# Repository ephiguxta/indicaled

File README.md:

# indicaled
Utiliza-se nove portas como input e outras nove portas para acionar um LED relativo ao input.

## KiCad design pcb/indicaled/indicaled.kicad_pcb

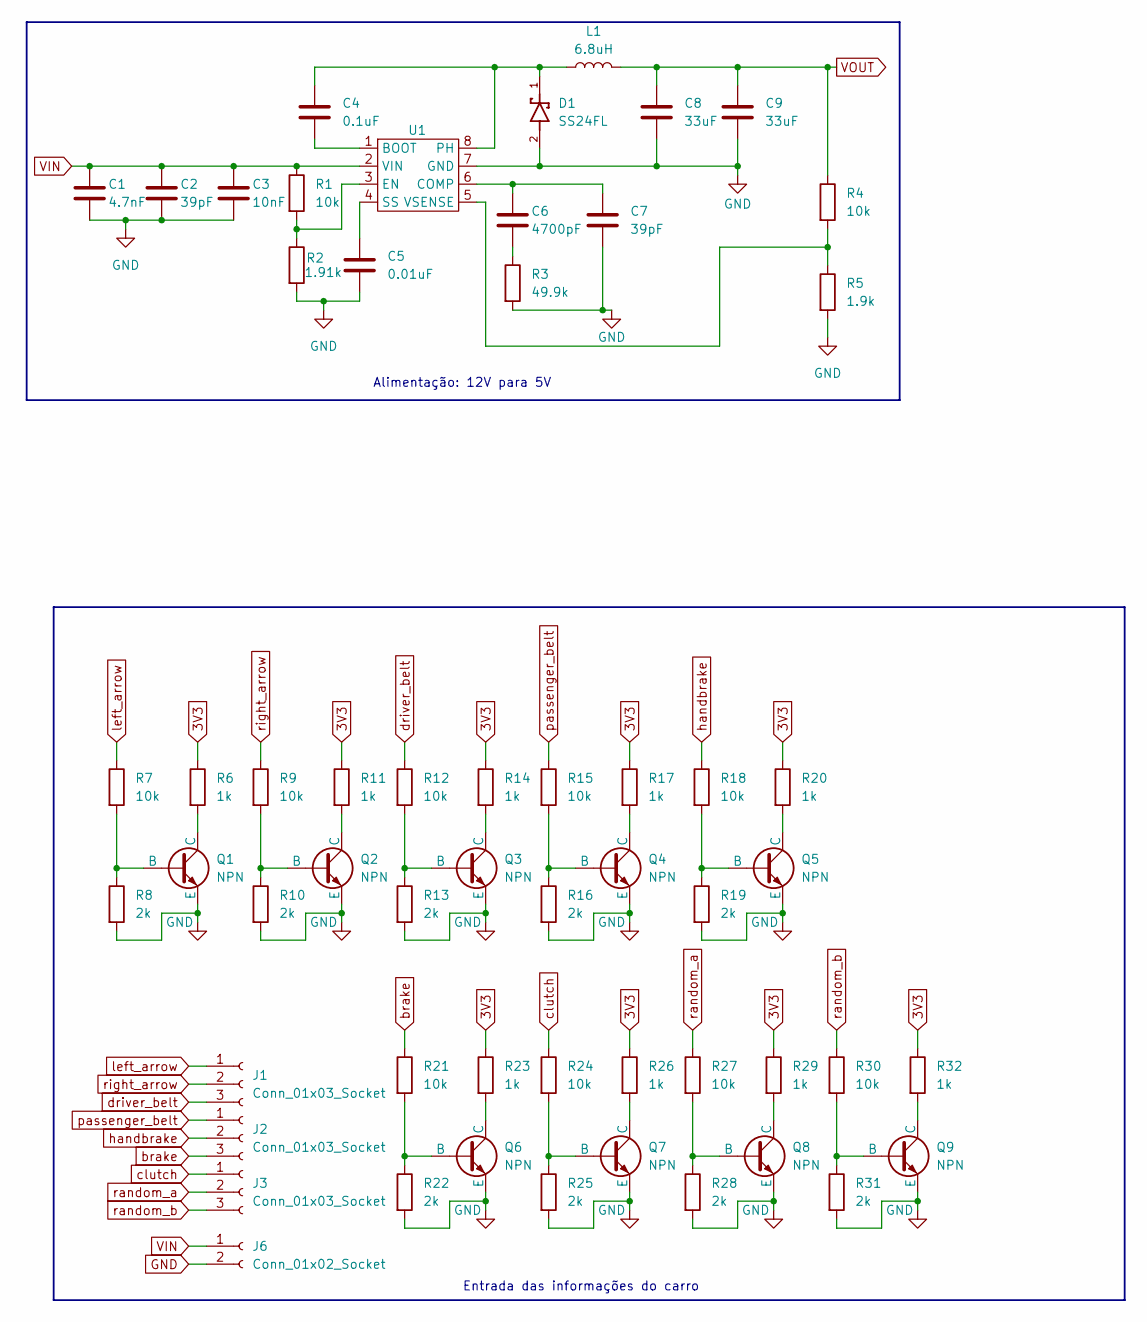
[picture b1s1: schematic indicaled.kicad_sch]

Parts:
C1: 4.7nF; C_1210_3225Metric
C2: 39pF; C_1210_3225Metric
C3: 10nF; C_1210_3225Metric
C4: 0.1uF; C_0402_1005Metric
C5: 0.01uF; C_0201_0603Metric
C6: 4700pF; C_0805_2012Metric
C7: 39pF; C_0805_2012Metric
C8, C9: 33uF; C_1210_3225Metric
D1: SS24FL; SS26; PARTREV N2306
J1, J2, J3: Conn_01x03_Socket
J6: Conn_01x02_Socket
L1: 6.8uH; L_APV_ANR5040
Q1, Q2, Q3, Q4, Q5, Q6, Q7, Q8, Q9: NPN; SOT-23
R1, R4: 10k; R_0402_1005Metric
R2: 1.91k; R_0402_1005Metric
R3: 49.9k; R_0402_1005Metric
R5: 1.9k; R_0402_1005Metric
R6, R11, R14, R17, R20, R23, R26, R29, R32: 1k; R_0201_0603Metric
R7, R9, R12, R15, R18, R21, R24, R27, R30: 10k; R_0201_0603Metric
R8, R10, R13, R16, R19, R22, R25, R28, R31: 2k; R_0201_0603Metric
U1: SOIC-8_3.9x4.9mm_P1.27mm

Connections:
3V3: R6.1, R11.1, R14.1, R17.1, R20.1, R23.1, R26.1, R29.1, R32.1
GND: C1.2, C2.2, C3.2, C5.2, C7.2, C8.2, C9.2, D1.2, Q1.3 (E), Q2.3 (E), Q3.3 (E), Q4.3 (E), Q5.3 (E), Q6.3 (E), Q7.3 (E), Q8.3 (E), Q9.3 (E), R2.2, R3.2, R5.2, R8.2, R10.2, R13.2, R16.2, R19.2, R22.2, R25.2, R28.2, R31.2, U1.7 (GND)
unnamed: C6.2, R3.1
unnamed: Q1.2 (B), R7.2, R8.1
unnamed: Q1.1 (C), R6.2
unnamed: Q2.2 (B), R9.2, R10.1
unnamed: Q2.1 (C), R11.2
unnamed: Q3.2 (B), R12.2, R13.1
unnamed: Q3.1 (C), R14.2
unnamed: Q4.2 (B), R15.2, R16.1
unnamed: Q4.1 (C), R17.2
unnamed: Q5.2 (B), R18.2, R19.1
unnamed: Q5.1 (C), R20.2
unnamed: Q6.2 (B), R21.2, R22.1
unnamed: Q6.1 (C), R23.2
unnamed: Q7.2 (B), R24.2, R25.1
unnamed: Q7.1 (C), R26.2
unnamed: Q8.2 (B), R27.2, R28.1
unnamed: Q8.1 (C), R29.2
unnamed: Q9.2 (B), R30.2, R31.1
unnamed: Q9.1 (C), R32.2
unnamed: C4.2, U1.1 (BOOT)
unnamed: C6.1, C7.1, U1.6 (COMP)
unnamed: R1.2, R2.1, U1.3 (EN)
unnamed: C4.1, D1.1, L1.1, U1.8 (PH)
unnamed: C5.1, U1.4 (SS)
unnamed: R4.2, R5.1, U1.5 (VSENSE)
VIN: C1.1, C2.1, C3.1, J6.1, R1.1, U1.2 (VIN)
VOUT: C8.1, C9.1, L1.2, R4.1
brake: J2.3, R21.1
clutch: J3.1, R24.1
driver_belt: J1.3, R12.1
handbrake: J2.2, R18.1
left_arrow: J1.1, R7.1
passenger_belt: J2.1, R15.1
random_a: J3.2, R27.1
random_b: J3.3, R30.1
right_arrow: J1.2, R9.1

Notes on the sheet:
Entrada das informações do carro
Alimentação: 12V para 5V

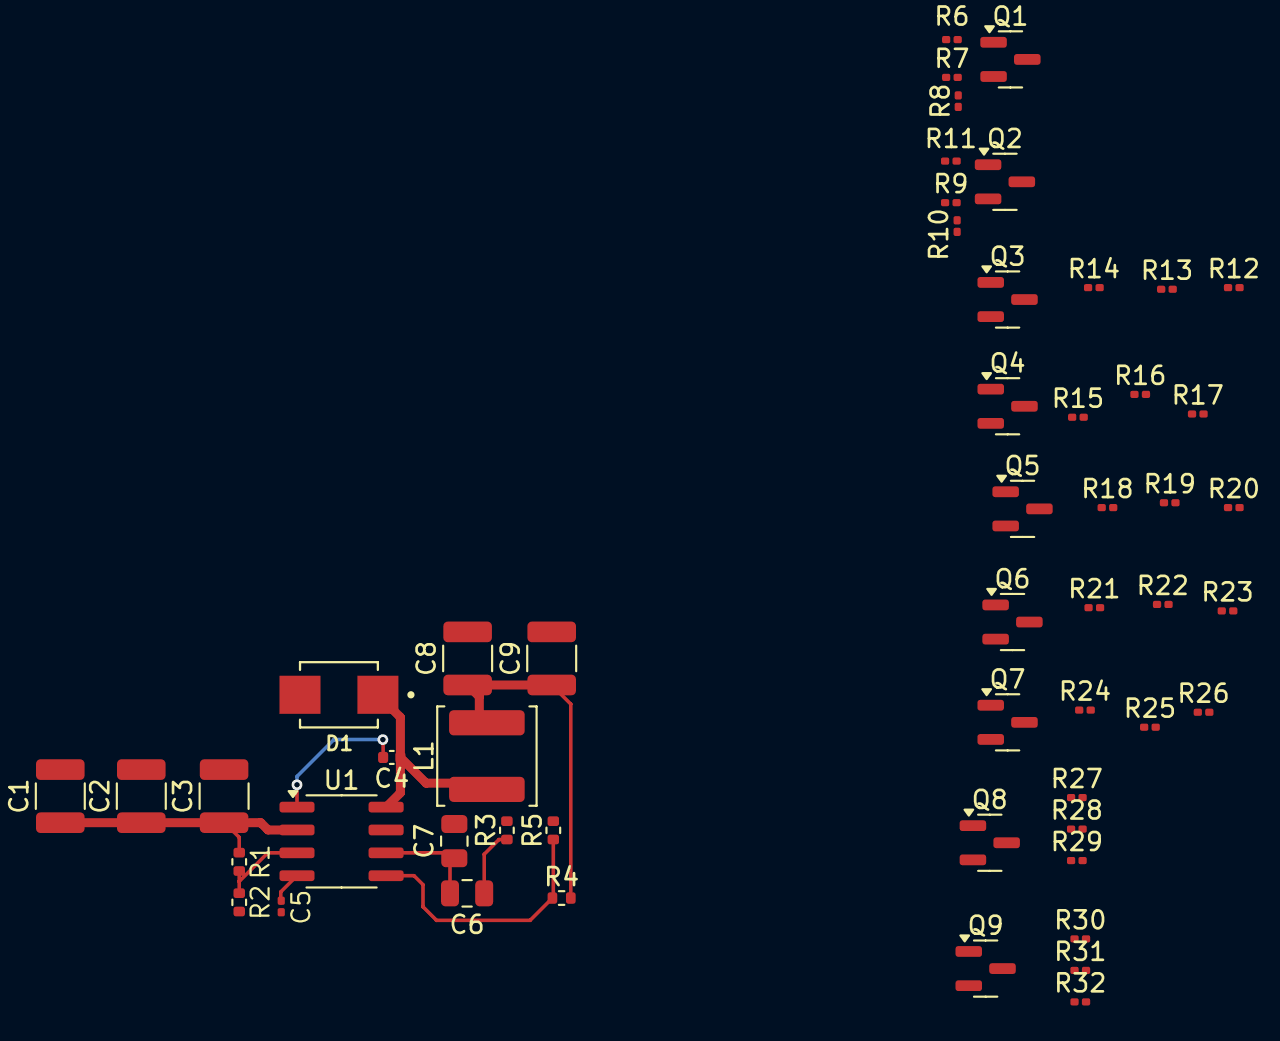
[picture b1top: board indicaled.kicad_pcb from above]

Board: 2 copper layers, 53 parts (0 on the bottom side), 29 nets.

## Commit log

2025-07-01 estrutura retirada do exemplo de testes unitários "unit_test"
2025-07-04 iniciando o circuito de alimentação, reduzindo 12V pra 5V com o TPS54331
2025-07-09 adicionando valores aos componentes
2025-07-10 adicionando footprints aos componentes do circuito de alimentação
2025-07-10 fazendo as ligações do circuito de alimentação e mudando o footprint do D1
2025-07-14 trocando os capacitores de acoplamento de 0201 para 1210
2025-07-14 colocando o datasheet da JLCPCB nos Cins e no TPS54331
2025-07-14 trocando o S26 por S24, adicionando alguns datasheets e reposicionando os componentes na PCB
2025-07-16 adicionando os transistores que vão retificar o sinal do caro pro ESP
2025-07-16 modificando o capacitor do pino SS
